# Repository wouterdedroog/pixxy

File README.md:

# Pixxy

Pixxy is a physical remote control for PixMob bracelets using a custom PCB. The PCB design is available in the 
[pixxy-kicad](pixxy-kicad) folder. I used KiCad 8 to design this PCB. There are currently two variations/revisions of 
this project. You're currently looking at the revision based on the RP2040 chip. 

There is also a revision based on the Raspberry Pi Pico, which is slightly cheaper and easier to assemble, but uses
micro USB instead of USB-C. This revision can be found [here](https://github.com//wouterdedroog/pixxy/tree/pico). The
MicroPython sourcecode found in the [src branch](https://github.com/wouterdedroog/pixxy/tree/src) is compatible with
both hardware versions.

## Branches
- [main](https://github.com/wouterdedroog/pixxy/tree/main) - Full project details and PCB design based on the RP2040 chip (has USB-C)
- [pico](https://github.com//wouterdedroog/pixxy/tree/pico) - PCB design based on the Raspberry Pi Pico (cheaper and easier to assemble)
- [src](https://github.com/wouterdedroog/pixxy/tree/src) - MicroPython source, compatible with both variations of Pixxy device

## Functionality
Both revisions are identical when it comes to the controls (switches and potentiometers) They both have a 4×4 button 
matrix. Eight of these buttons are used for selecting preset colours. The ninth button selects a custom colour, using 
the red/green/blue values from the potentiometers above the buttons (marked RV1, RV2 and RV3).

The Fade and Flash buttons are used to send the selected colour to the IR LED (connected to a 2N3904 transistor). The
Once / Repeat switch can be used to send the command once or multiple times.

For X2 bracelets (the ones being used at Taylor Swift concerts), it is possible to set a colour indefinitely. The On and
Off buttons are used for this. The Taylor End button sends the end/go home signal used at concerts, which causes the
bracelet to loop through a set of colours until the battery runs out. The rainbow effect does the same effect, but with
the colours of the rainbow in order.

When the Speed Set button is held down, the value of the RV3/Blue potentiometer influences the speed of the commands. 
This means the potentiometer influences how long a fade or flash command lasts, and how much time is in between these
commands if the switch is in the repeat position.

Pixxy also responds to commands over serial. You can use [this site](https://wissenhinterdenkulissen.de/armband/) which
uses WebSerial, or the Python sender scripts in the 
[pixmob-ir-reverse-engineering repo](https://github.com/danielweidman/pixmob-ir-reverse-engineering/).

## Schematic
The PCB and schematic were made using KiCad 8. The project files are available in the
[pixxy-kicad directory](pixxy-kicad). A screenshot of the schematic can be found below:

## Thanks
This project wouldn't have been possible without the research available in the
[pixmob-ir-reverse-engineering](https://github.com/danielweidman/pixmob-ir-reverse-engineering/) and 
[PixMob_IR](https://github.com/jamesw343/PixMob_IR/) repositories. The knowledge available in the
[PIXMOD Discord](https://discord.com/invite/UYqTjC7xp3) has also been super helpful.

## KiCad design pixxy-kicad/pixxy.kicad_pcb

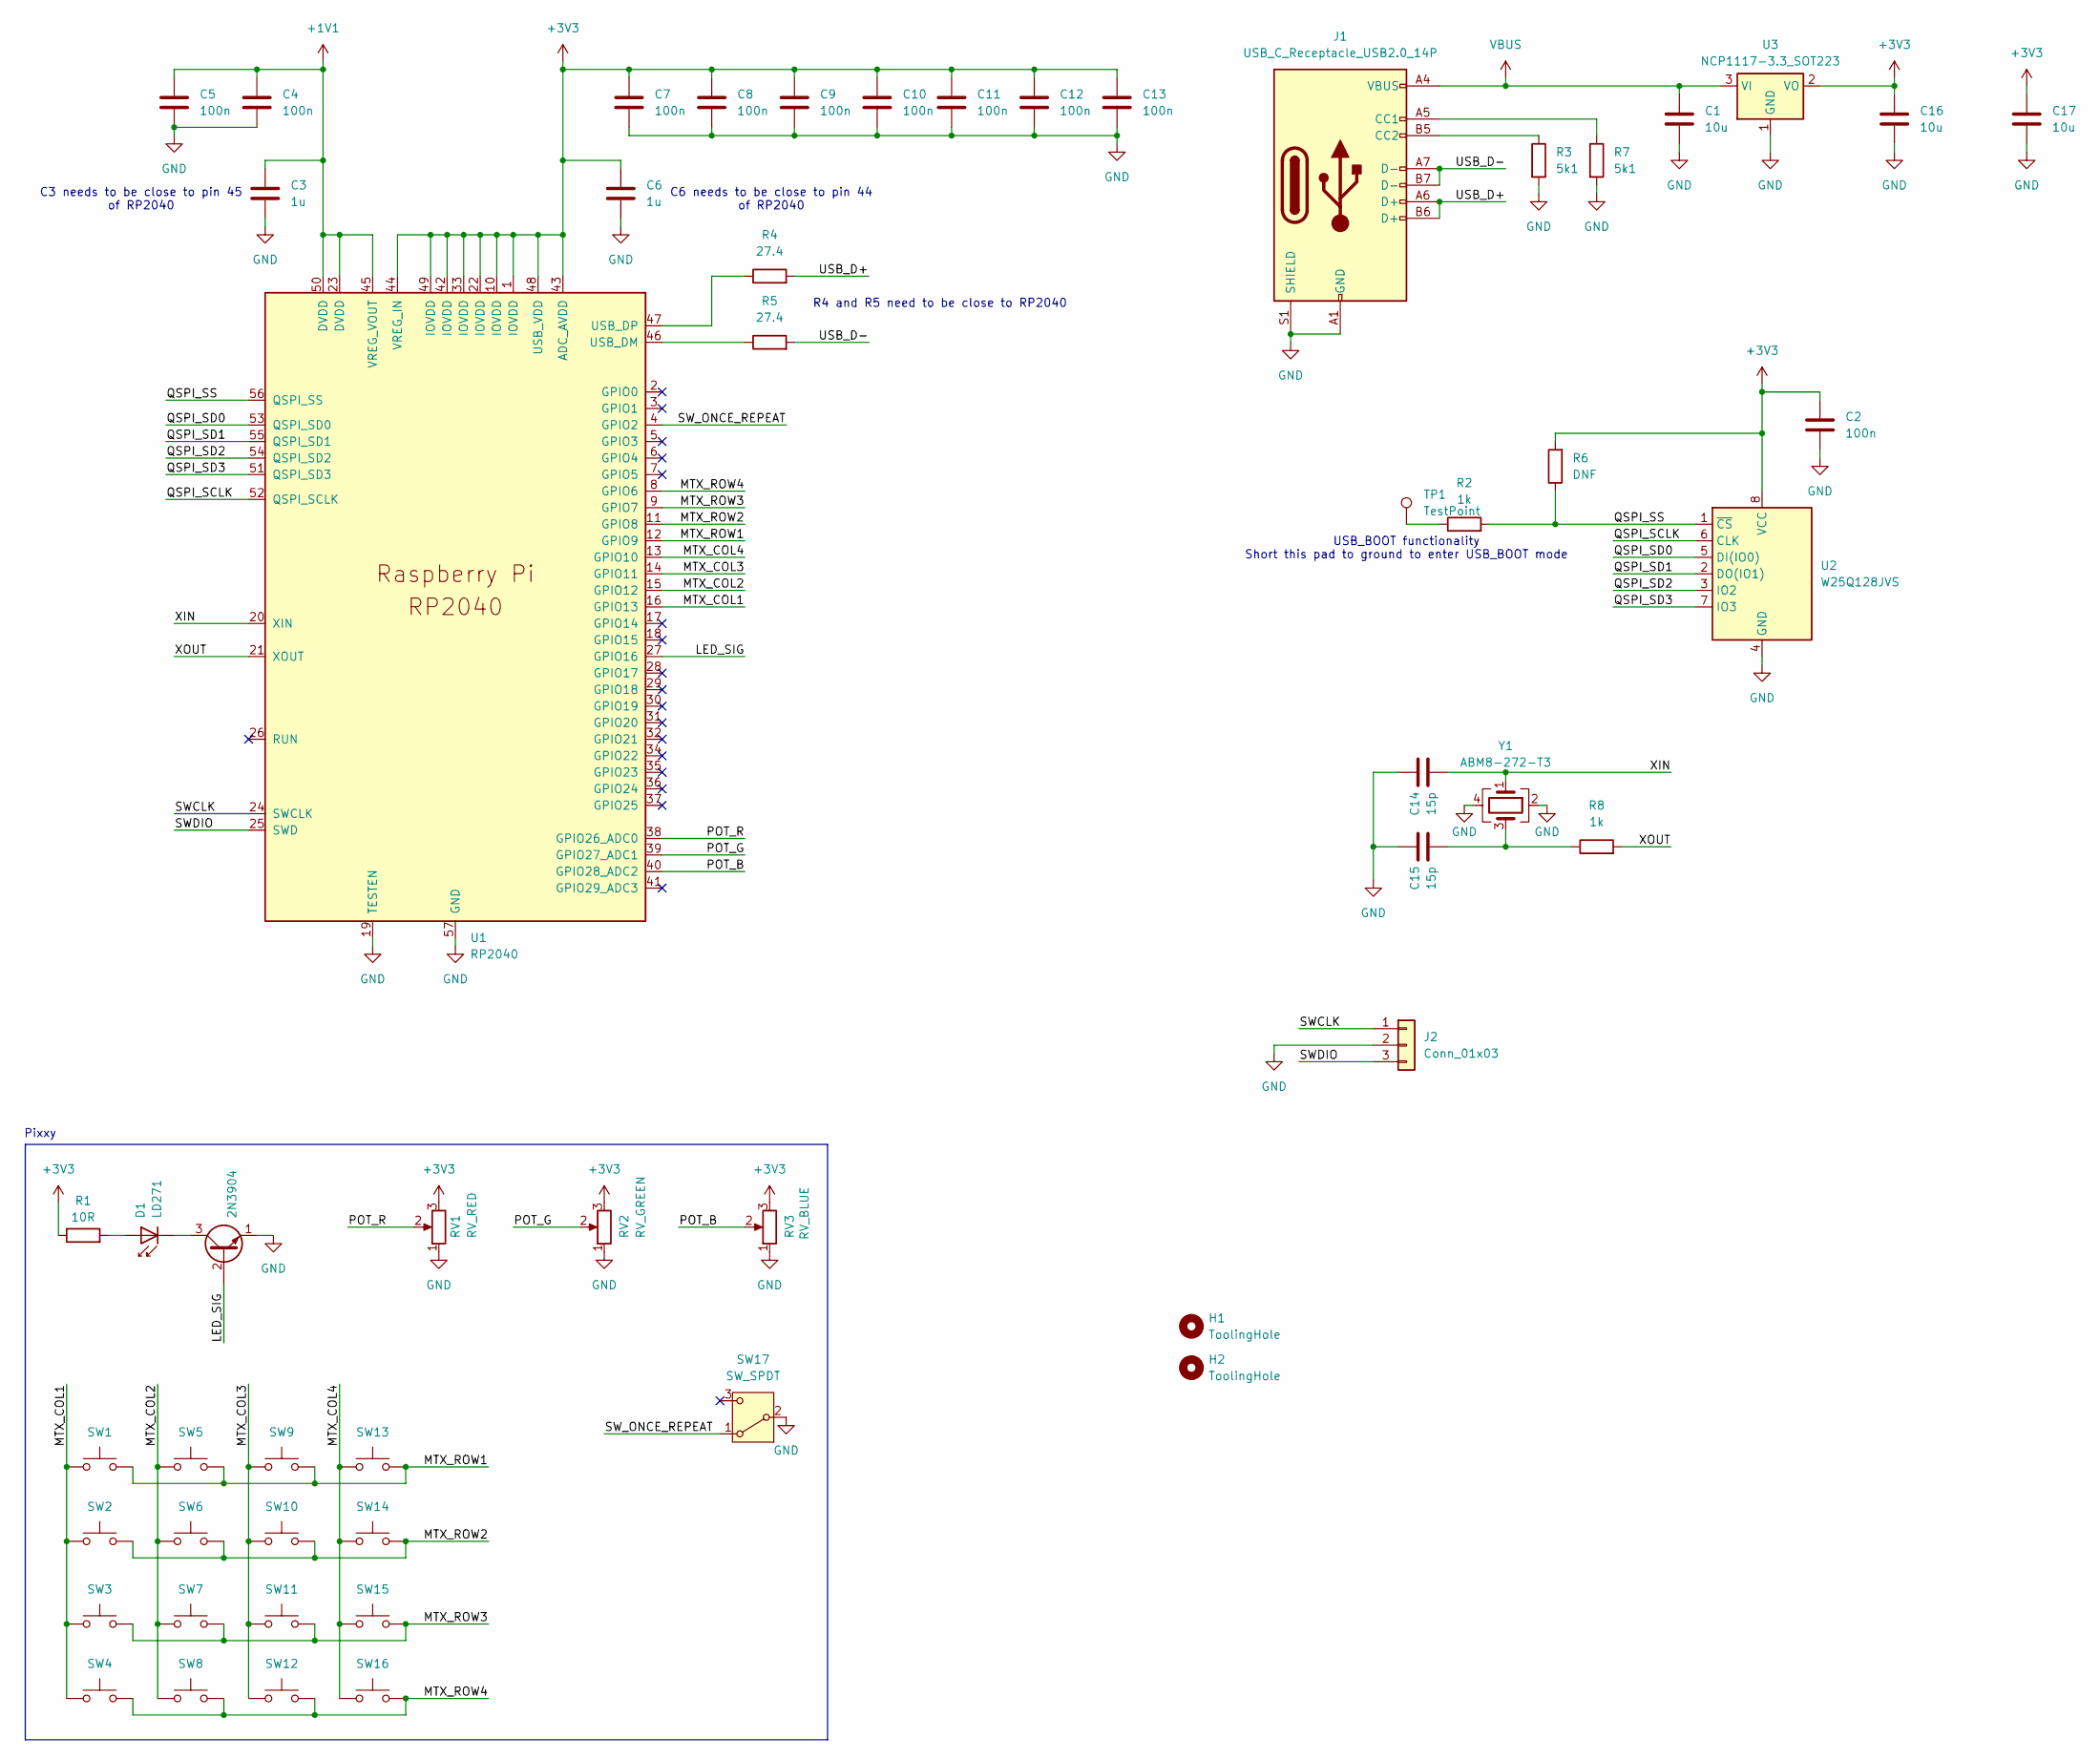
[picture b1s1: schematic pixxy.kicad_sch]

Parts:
C1, C16, C17: 10u; C_0805_2012Metric; LCSC C15850
C2, C4, C5, C7, C8, C9, C10, C11, C12, C13: 100n; C_0402_1005Metric; LCSC C307331
C3, C6: 1u; C_0402_1005Metric; LCSC C52923
C14, C15: 15p; C_0402_1005Metric; LCSC C1548
D1: LD271; LED_D5.0mm_IRGrey
H1, H2: ToolingHole; MountingHole_1.152mm
J1: USB_C_Receptacle_USB2.0_14P; USB_C_Receptacle_G-Switch_GT-USB-7010ASV; LCSC C2988369
J2: Conn_01x03; JST_SH_SM03B-SRSS-TB_1x03-1MP_P1.00mm_Horizontal
Q1: 2N3904; TO-92_Inline
R1: 10R; R_Axial_DIN0207_L6.3mm_D2.5mm_P10.16mm_Horizontal
R2, R8: 1k; R_0402_1005Metric; LCSC C11702
R3, R7: 5k1; R_0402_1005Metric; LCSC C25905
R4, R5: 27.4; R_0402_1005Metric; LCSC C321420
R6: DNF; R_0402_1005Metric
RV1: RV_RED; Potentiometer_Alps_RK09K_Single_Vertical
RV2: RV_GREEN; Potentiometer_Alps_RK09K_Single_Vertical
RV3: RV_BLUE; Potentiometer_Alps_RK09K_Single_Vertical
SW1, SW2, SW3, SW4, SW5, SW6, SW7, SW8, SW9, SW10, SW11, SW12, SW13, SW14, SW15, SW16: SW_PUSH_6mm
SW17: SW_SPDT; SW_Slide-03_Wuerth-WS-SLTV_10x2.5x6.4_P2.54mm
TP1: TestPoint; TestPoint_Pad_1.5x1.5mm
U1: RP2040; QFN-56-1EP_7x7mm_P0.4mm_EP3.2x3.2mm; LCSC C2040
U2: W25Q128JVS; SOIC-8_5.23x5.23mm_P1.27mm; LCSC C97521
U3: NCP1117-3.3_SOT223; SOT-223-3_TabPin2; LCSC C26537
Y1: ABM8-272-T3; Crystal_SMD_3225-4Pin_3.2x2.5mm; LCSC C20625731

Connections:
+1V1: C3.1, C4.1, C5.1, U1.23 (DVDD), U1.45 (VREG_VOUT), U1.50 (DVDD)
+3V3: C2.1, C6.1, C7.1, C8.1, C9.1, C10.1, C11.1, C12.1, C13.1, C16.1, C17.1, R1.1, R6.2, RV1.3, RV2.3, RV3.3, U1.1 (IOVDD), U1.10 (IOVDD), U1.22 (IOVDD), U1.33 (IOVDD), U1.42 (IOVDD), U1.43 (ADC_AVDD), U1.44 (VREG_IN), U1.48 (USB_VDD), U1.49 (IOVDD), U2.8 (VCC), U3.2 (VO)
/LED_SIG: Q1.2 (B), U1.27 (GPIO16)
/MTX_COL1: SW1.1, SW2.1, SW3.1, SW4.1, U1.16 (GPIO13)
/MTX_COL2: SW5.1, SW6.1, SW7.1, SW8.1, U1.15 (GPIO12)
/MTX_COL3: SW9.1, SW10.1, SW11.1, SW12.1, U1.14 (GPIO11)
/MTX_COL4: SW13.1, SW14.1, SW15.1, SW16.1, U1.13 (GPIO10)
/MTX_ROW1: SW1.2, SW5.2, SW9.2, SW13.2, U1.12 (GPIO9)
/MTX_ROW2: SW2.2, SW6.2, SW10.2, SW14.2, U1.11 (GPIO8)
/MTX_ROW3: SW3.2, SW7.2, SW11.2, SW15.2, U1.9 (GPIO7)
/MTX_ROW4: SW4.2, SW8.2, SW12.2, SW16.2, U1.8 (GPIO6)
/POT_B: RV3.2, U1.40 (GPIO28_ADC2)
/POT_G: RV2.2, U1.39 (GPIO27_ADC1)
/POT_R: RV1.2, U1.38 (GPIO26_ADC0)
/QSPI_SCLK: U1.52 (QSPI_SCLK), U2.6 (CLK)
/QSPI_SD0: U1.53 (QSPI_SD0), U2.5 (DI(IO0))
/QSPI_SD1: U1.55 (QSPI_SD1), U2.2 (DO(IO1))
/QSPI_SD2: U1.54 (QSPI_SD2), U2.3 (IO2)
/QSPI_SD3: U1.51 (QSPI_SD3), U2.7 (IO3)
/QSPI_SS: R2.2, R6.1, U1.56 (QSPI_SS), U2.1 (~CS)
/SWCLK: J2.1, U1.24 (SWCLK)
/SWDIO: J2.3, U1.25 (SWD)
/SW_ONCE_REPEAT: SW17.1 (A), U1.4 (GPIO2)
/USB_D+: J1.A6 (D+), J1.B6 (D+), R4.2
/USB_D-: J1.A7 (D-), J1.B7 (D-), R5.2
/XIN: C14.2, U1.20 (XIN), Y1.1
/XOUT: R8.2, U1.21 (XOUT)
GND: C1.2, C2.2, C3.2, C4.2, C5.2, C6.2, C7.2, C8.2, C9.2, C10.2, C11.2, C12.2, C13.2, C14.1, C15.1, C16.2, C17.2, J1.A1 (GND), J1.A12 (GND), J1.B1 (GND), J1.B12 (GND), J1.S1 (SHIELD), J2.2, Q1.1 (E), R3.2, R7.2, RV1.1, RV2.1, RV3.1, SW17.2 (B), U1.19 (TESTEN), U1.57 (GND), U2.4 (GND), U3.1 (GND), Y1.2, Y1.4
unnamed: C15.2, R8.1, Y1.3
unnamed: D1.2 (A), R1.2
unnamed: D1.1 (K), Q1.3 (C)
unnamed: J1.A5 (CC1), R7.1
unnamed: J1.B5 (CC2), R3.1
unnamed: R2.1, TP1.1
unnamed: R5.1, U1.46 (USB_DM)
unnamed: R4.1, U1.47 (USB_DP)
VBUS: C1.1, J1.A4 (VBUS), J1.A9 (VBUS), J1.B4 (VBUS), J1.B9 (VBUS), U3.3 (VI)

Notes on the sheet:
C6 needs to be close to pin 44 of RP2040
C3 needs to be close to pin 45 of RP2040
Pixxy
USB_BOOT functionality Short this pad to ground to enter USB_BOOT mode
R4 and R5 need to be close to RP2040

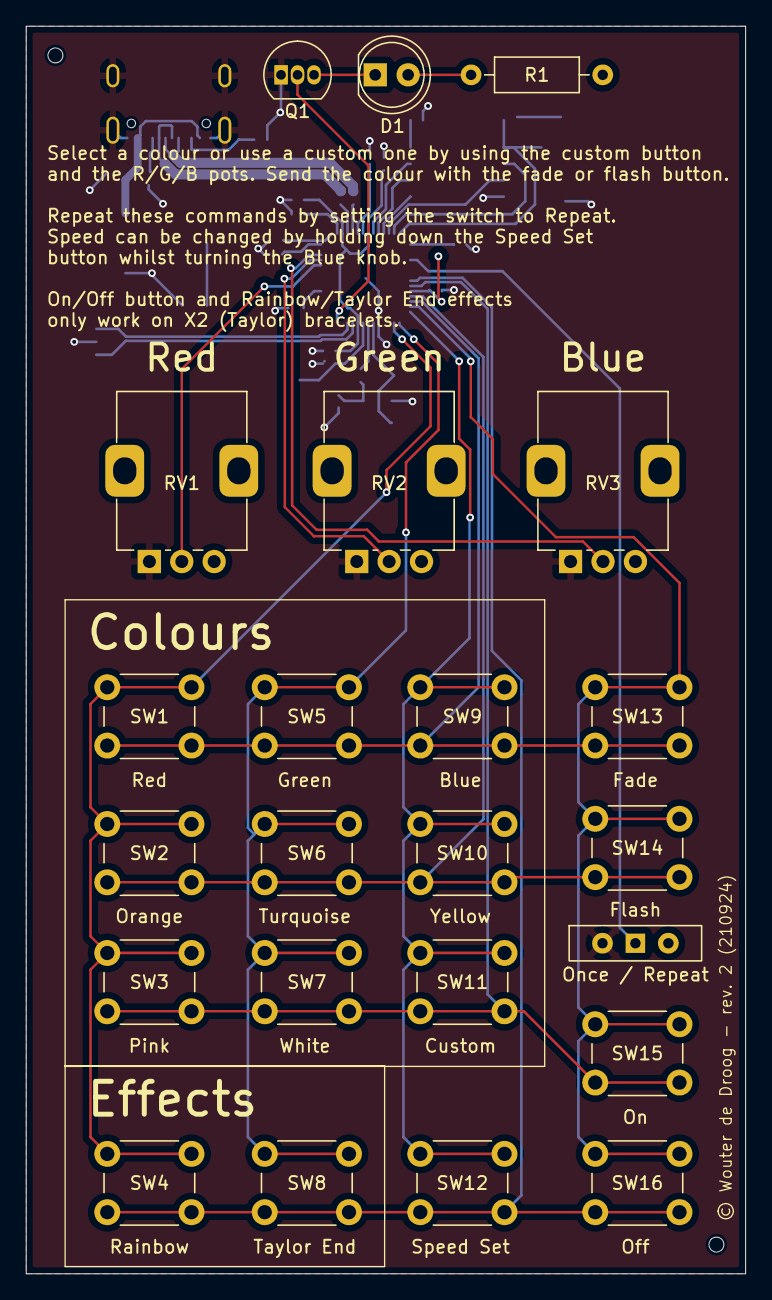
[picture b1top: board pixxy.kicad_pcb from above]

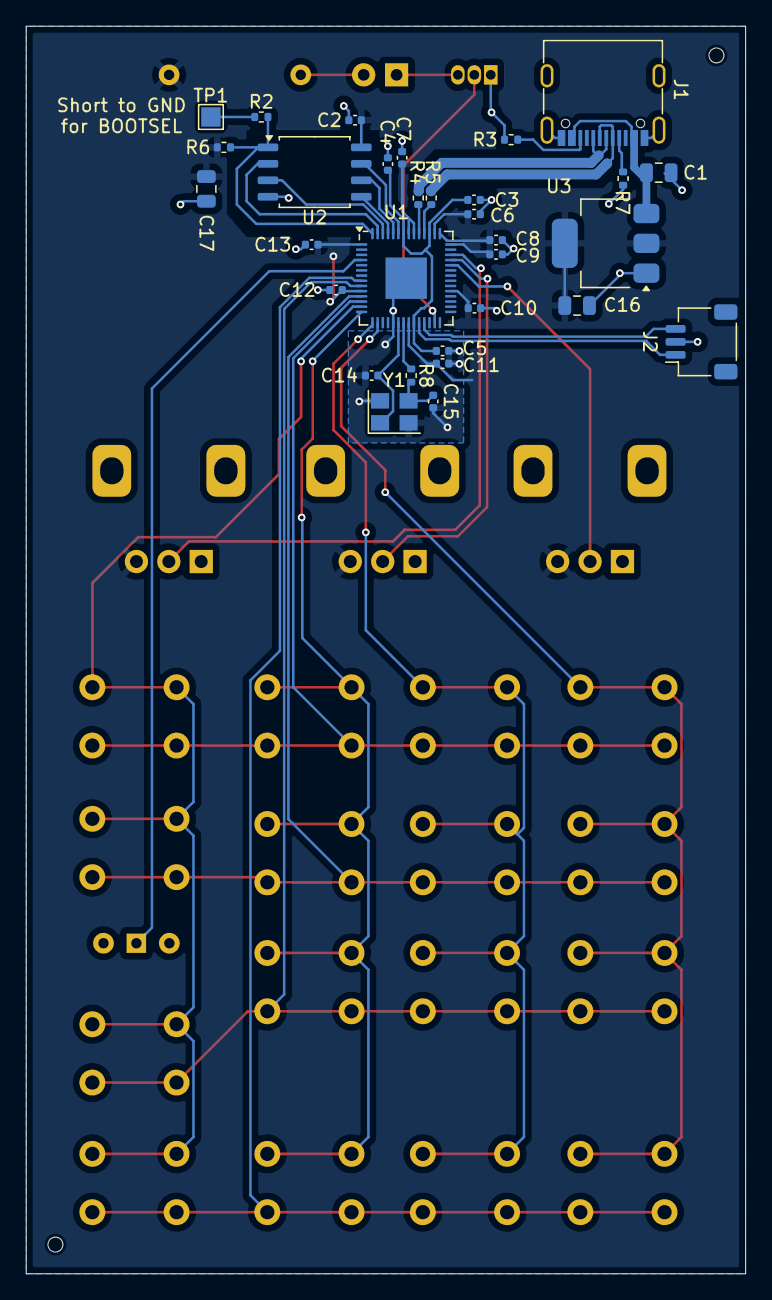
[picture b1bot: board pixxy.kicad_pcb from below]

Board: 2 copper layers, 55.5 x 96.2 mm, 56 parts (31 on the bottom side), 37 nets.

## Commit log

2024-08-21 Add README and initial revision of PCB
2024-08-21 Add current Python code
    Current code does not yet support the Once / Repeat switch and Speed Set button
2024-08-30 Add initial working software, improve PCB design
2024-09-05 Fix repeat effect stopping if button on row 1 is used
2024-09-07 Add rev1 pcb files
2024-09-16 Add RP2040-based schematic
2024-09-21 Improved schematic and finished pcb for rev2
2024-10-06 Add source code
2024-10-06 Change README for Pico branch
2024-10-06 Remove src from RP2040 branch, update README
2024-10-06 Use ADC instead to remove picozero dependency

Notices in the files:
pixxy-kicad/pixxy.kicad_pcb:
© Wouter de Droog - rev. 2 (210924)
